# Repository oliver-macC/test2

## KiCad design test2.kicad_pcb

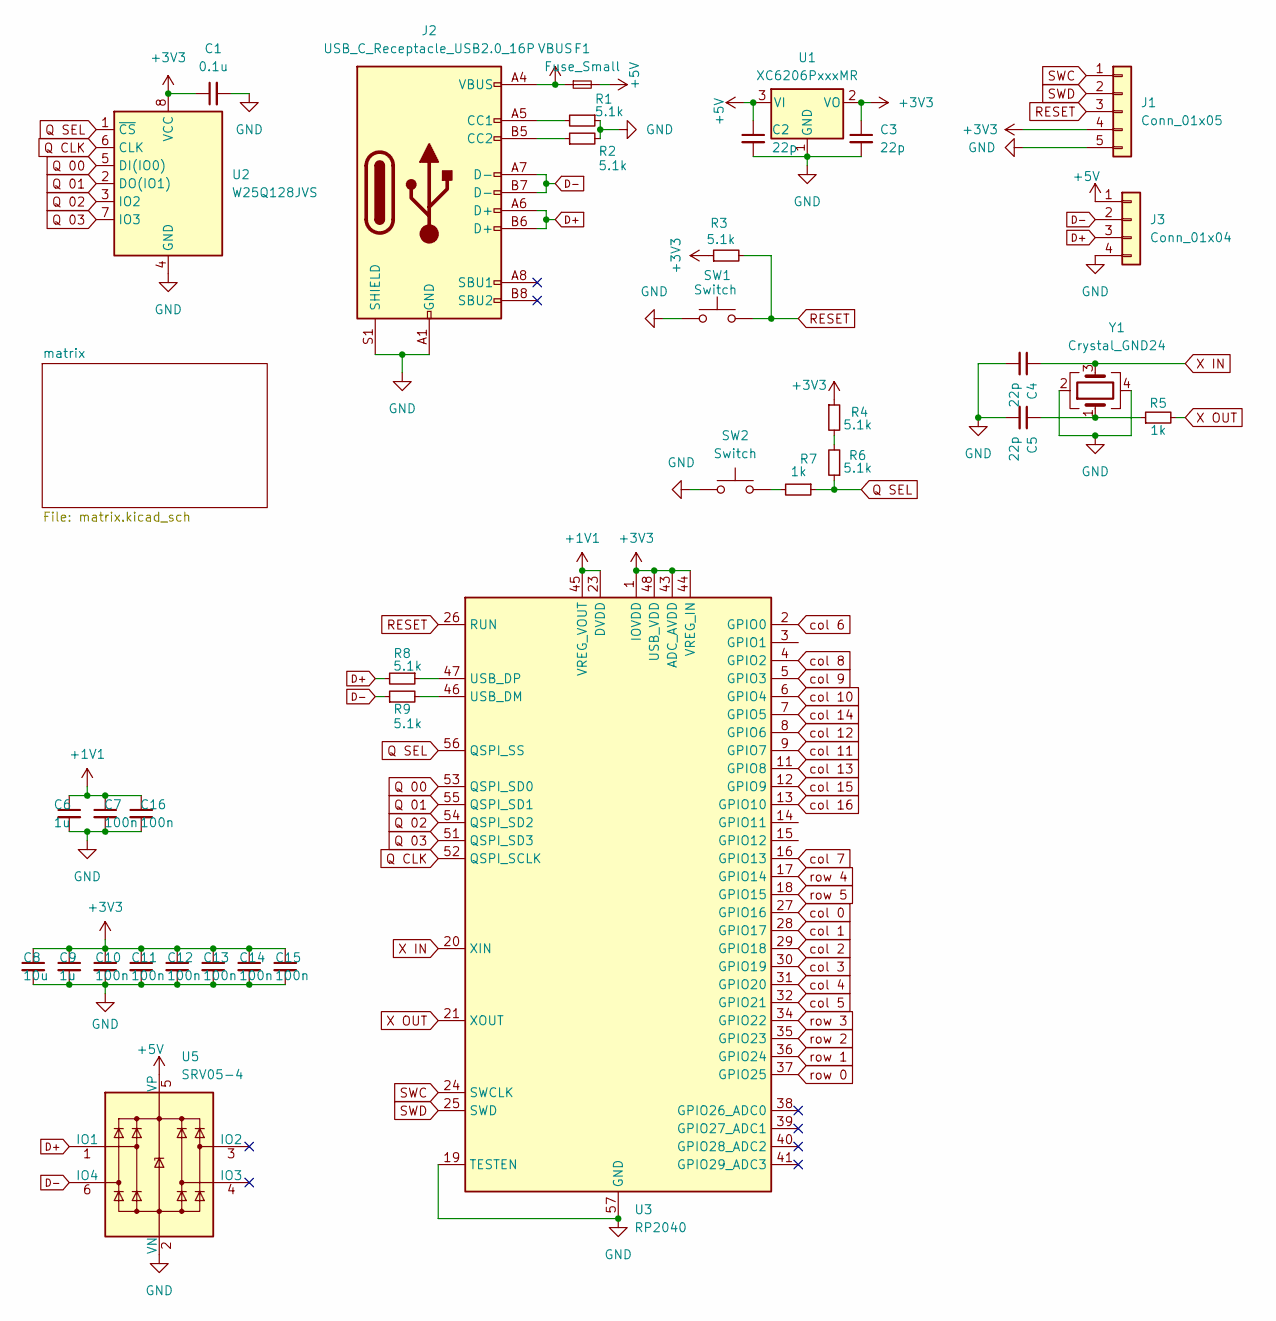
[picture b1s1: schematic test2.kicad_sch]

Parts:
C1: 0.1u; C_0402_1005Metric
C2, C3, C4, C5: 22p; C_0402_1005Metric
C6, C9: 1u; C_0402_1005Metric
C7, C10, C11, C12, C13, C14, C15, C16: 100n; C_0402_1005Metric
C8: 10u; C_0603_1608Metric
F1: Fuse_Small; Fuse_1206_3216Metric
J1: Conn_01x05; PinHeader_1x05_P2.54mm_Vertical
J2: USB_C_Receptacle_USB2.0_16P; USB_C_Receptacle_HRO_TYPE-C-31-M-12
J3: Conn_01x04; JST_SH_SM04B-SRSS-TB_1x04-1MP_P1.00mm_Horizontal
R1, R2, R3, R4, R6, R8, R9: 5.1k; R_0402_1005Metric
R5, R7: 1k; R_0402_1005Metric
SW1, SW2: Switch; SW_Push_1P1T_XKB_TS-1187A
U1: XC6206PxxxMR; SOT-23-3
U2: W25Q128JVS; SOIC-8_5.23x5.23mm_P1.27mm
U3: RP2040; QFN-56-1EP_7x7mm_P0.4mm_EP3.2x3.2mm
U5: SRV05-4; SOT-23-6-routable
Y1: Crystal_GND24; Crystal_SMD_3225-4Pin_3.2x2.5mm

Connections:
+1V1: C6.1, C7.1, C16.1, U3.23 (DVDD), U3.45 (VREG_VOUT), U3.50 (DVDD)
+3V3: C1.1, C3.1, C8.1, C9.1, C10.1, C11.1, C12.1, C13.1, C14.1, C15.1, J1.4, R3.1, R4.1, U1.2 (VO), U2.8 (VCC), U3.1 (IOVDD), U3.10 (IOVDD), U3.22 (IOVDD), U3.33 (IOVDD), U3.42 (IOVDD), U3.43 (ADC_AVDD), U3.44 (VREG_IN), U3.48 (USB_VDD), U3.49 (IOVDD)
+5V: C2.1, F1.2, J3.1, U1.3 (VI), U5.5 (VP)
D+: J2.A6 (D+), J2.B6 (D+), J3.3, R8.2, U5.1 (IO1)
D-: J2.A7 (D-), J2.B7 (D-), J3.2, R9.1, U5.6 (IO4)
GND: C1.2, C2.2, C3.2, C4.2, C5.2, C6.2, C7.2, C8.2, C9.2, C10.2, C11.2, C12.2, C13.2, C14.2, C15.2, C16.2, J1.5, J2.A1 (GND), J2.A12 (GND), J2.B1 (GND), J2.B12 (GND), J2.S1 (SHIELD), J3.4, R1.1, R2.2, SW1.1, SW2.1, U1.1 (GND), U2.4 (GND), U3.19 (TESTEN), U3.57 (GND), U5.2 (VN), Y1.2, Y1.4
unnamed: C5.1, R5.1, Y1.1
unnamed: J2.A5 (CC1), R1.2
unnamed: J2.B5 (CC2), R2.1
unnamed: R4.2, R6.2
unnamed: R7.2, SW2.2
unnamed: R9.2, U3.46 (USB_DM)
unnamed: R8.1, U3.47 (USB_DP)
Q 00: U2.5 (DI(IO0)), U3.53 (QSPI_SD0)
Q 01: U2.2 (DO(IO1)), U3.55 (QSPI_SD1)
Q 02: U2.3 (IO2), U3.54 (QSPI_SD2)
Q 03: U2.7 (IO3), U3.51 (QSPI_SD3)
Q CLK: U2.6 (CLK), U3.52 (QSPI_SCLK)
Q SEL: R6.1, R7.1, U2.1 (~CS), U3.56 (QSPI_SS)
RESET: J1.3, R3.2, SW1.2, U3.26 (RUN)
SWC: J1.1, U3.24 (SWCLK)
SWD: J1.2, U3.25 (SWD)
VBUS: F1.1, J2.A4 (VBUS), J2.A9 (VBUS), J2.B4 (VBUS), J2.B9 (VBUS)
X IN: C4.1, U3.20 (XIN), Y1.3
X OUT: R5.2, U3.21 (XOUT)
col 0: U3.27 (GPIO16); also elsewhere on the board
col 1: U3.28 (GPIO17); also elsewhere on the board
col 2: U3.29 (GPIO18); also elsewhere on the board
col 3: U3.30 (GPIO19); also elsewhere on the board
col 4: U3.31 (GPIO20); also elsewhere on the board
col 5: U3.32 (GPIO21); also elsewhere on the board
col 6: U3.2 (GPIO0); also elsewhere on the board
col 7: U3.16 (GPIO13); also elsewhere on the board
col 8: U3.4 (GPIO2); also elsewhere on the board
col 9: U3.5 (GPIO3); also elsewhere on the board
col 10: U3.6 (GPIO4); also elsewhere on the board
col 11: U3.9 (GPIO7); also elsewhere on the board
col 12: U3.8 (GPIO6); also elsewhere on the board
col 13: U3.11 (GPIO8); also elsewhere on the board
col 14: U3.7 (GPIO5); also elsewhere on the board
col 15: U3.12 (GPIO9); also elsewhere on the board
col 16: U3.13 (GPIO10); also elsewhere on the board
row 0: U3.37 (GPIO25); also elsewhere on the board
row 1: U3.36 (GPIO24); also elsewhere on the board
row 2: U3.35 (GPIO23); also elsewhere on the board
row 3: U3.34 (GPIO22); also elsewhere on the board
row 4: U3.17 (GPIO14); also elsewhere on the board
row 5: U3.18 (GPIO15); also elsewhere on the board

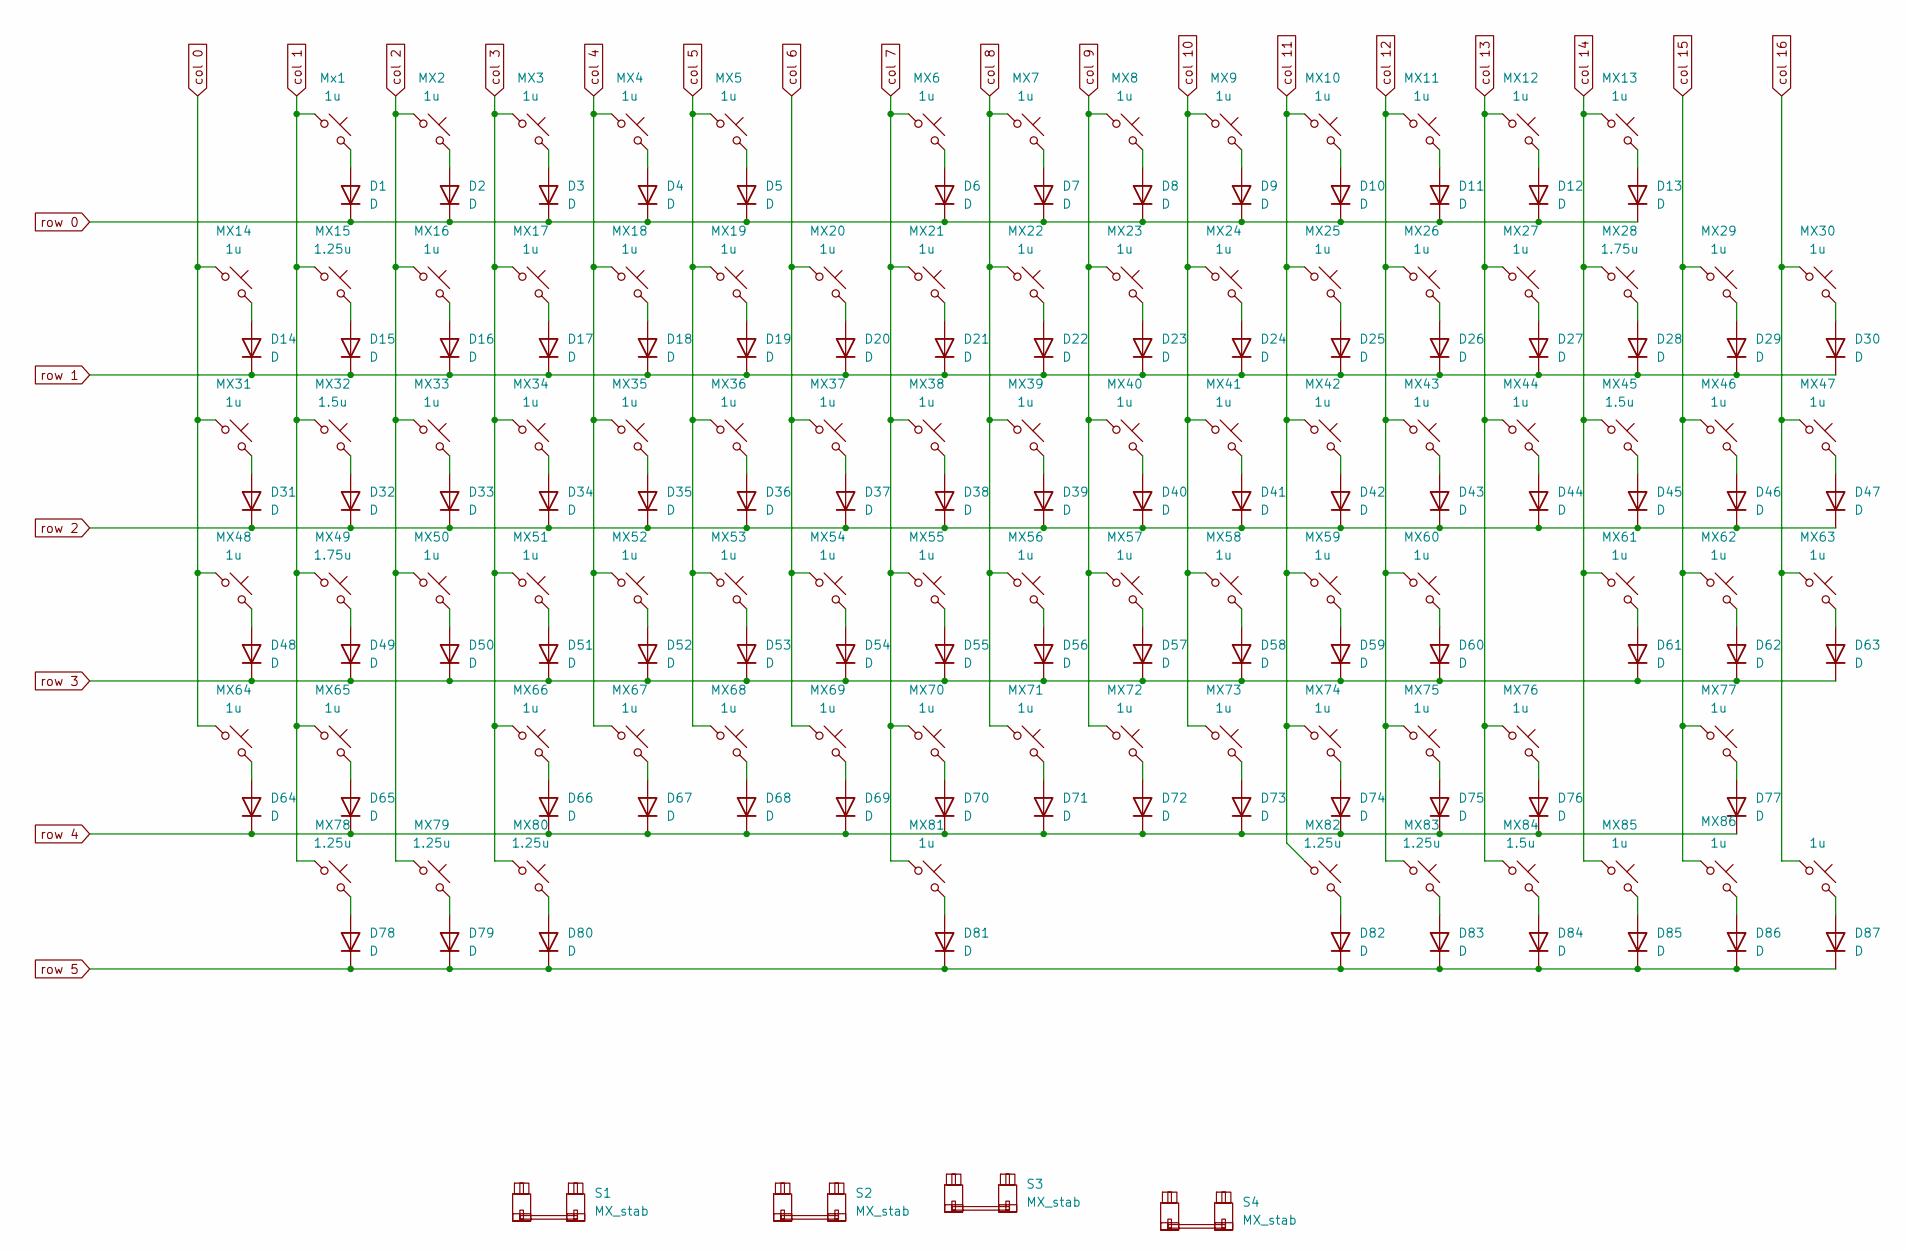
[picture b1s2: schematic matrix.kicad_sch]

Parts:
D1, D2, D3, D4, D5, D6, D7, D8, D9, D10, D11, D12, D13, D14, D15, D16, D17, D18, D19, D20, D21, D22, D23, D24, D25, D26, D27, D28, D29, D30, D31, D32, D33, D34, D35, D36, D37, D38, D39, D40, D41, D42, D43, D44, D45, D46, D47, D48, D49, D50, D51, D52, D53, D54, D55, D56, D57, D58, D59, D60, D61, D62, D63, D64, D65, D66, D67, D68, D69, D70, D71, D72, D73, D74, D75, D76, D77, D78, D79, D80, D81, D82, D83, D84, D85, D86, D87: D; D_SOD-123
MX2, MX3, MX4, MX5, MX6, MX7, MX8, MX9, MX10, MX11, MX12, MX13, MX14, MX16, MX17, MX18, MX19, MX20, MX21, MX22, MX23, MX24, MX25, MX26, MX27, MX29, MX30, MX31, MX33, MX34, MX35, MX36, MX37, MX38, MX39, MX40, MX41, MX42, MX43, MX44, MX46, MX47, MX48, MX50, MX51, MX52, MX53, MX54, MX55, MX56, MX57, MX58, MX59, MX60, MX61, MX62, MX63, MX64, MX65, MX66, MX67, MX68, MX69, MX70, MX71, MX72, MX73, MX74, MX75, MX76, MX77, MX81, MX85, MX86, MX87: 1u; SW_MX_HS_CPG151101S11_1u
MX15, MX78, MX79, MX80, MX82, MX83: 1.25u; SW_MX_HS_CPG151101S11_1.25u
MX28, MX49: 1.75u; SW_MX_HS_CPG151101S11_1.75u
MX32, MX45, MX84: 1.5u; SW_MX_HS_CPG151101S11_1.5u
Mx1: 1u; SW_MX_HS_CPG151101S11_1u
S1: MX_stab; STAB_MX_P_6.25u
S2, S3, S4: MX_stab; STAB_MX_P_2.25u

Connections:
unnamed: D1.2 (A), Mx1.2
unnamed: D2.2 (A), MX2.2
unnamed: D3.2 (A), MX3.2
unnamed: D4.2 (A), MX4.2
unnamed: D5.2 (A), MX5.2
unnamed: D6.2 (A), MX6.2
unnamed: D7.2 (A), MX7.2
unnamed: D8.2 (A), MX8.2
unnamed: D9.2 (A), MX9.2
unnamed: D10.2 (A), MX10.2
unnamed: D11.2 (A), MX11.2
unnamed: D12.2 (A), MX12.2
unnamed: D13.2 (A), MX13.2
unnamed: D14.2 (A), MX14.2
unnamed: D15.2 (A), MX15.2
unnamed: D16.2 (A), MX16.2
unnamed: D17.2 (A), MX17.2
unnamed: D18.2 (A), MX18.2
unnamed: D19.2 (A), MX19.2
unnamed: D20.2 (A), MX20.2
unnamed: D21.2 (A), MX21.2
unnamed: D22.2 (A), MX22.2
unnamed: D23.2 (A), MX23.2
unnamed: D24.2 (A), MX24.2
unnamed: D25.2 (A), MX25.2
unnamed: D26.2 (A), MX26.2
unnamed: D27.2 (A), MX27.2
unnamed: D28.2 (A), MX28.2
unnamed: D29.2 (A), MX29.2
unnamed: D30.2 (A), MX30.2
unnamed: D31.2 (A), MX31.2
unnamed: D32.2 (A), MX32.2
unnamed: D33.2 (A), MX33.2
unnamed: D34.2 (A), MX34.2
unnamed: D35.2 (A), MX35.2
unnamed: D36.2 (A), MX36.2
unnamed: D37.2 (A), MX37.2
unnamed: D38.2 (A), MX38.2
unnamed: D39.2 (A), MX39.2
unnamed: D40.2 (A), MX40.2
unnamed: D41.2 (A), MX41.2
unnamed: D42.2 (A), MX42.2
unnamed: D43.2 (A), MX43.2
unnamed: D44.2 (A), MX44.2
unnamed: D45.2 (A), MX45.2
unnamed: D46.2 (A), MX46.2
unnamed: D47.2 (A), MX47.2
unnamed: D48.2 (A), MX48.2
unnamed: D49.2 (A), MX49.2
unnamed: D50.2 (A), MX50.2
unnamed: D51.2 (A), MX51.2
unnamed: D52.2 (A), MX52.2
unnamed: D53.2 (A), MX53.2
unnamed: D54.2 (A), MX54.2
unnamed: D55.2 (A), MX55.2
unnamed: D56.2 (A), MX56.2
unnamed: D57.2 (A), MX57.2
unnamed: D58.2 (A), MX58.2
unnamed: D59.2 (A), MX59.2
unnamed: D60.2 (A), MX60.2
unnamed: D61.2 (A), MX61.2
unnamed: D62.2 (A), MX62.2
unnamed: D63.2 (A), MX63.2
unnamed: D64.2 (A), MX64.2
unnamed: D65.2 (A), MX65.2
unnamed: D66.2 (A), MX66.2
unnamed: D67.2 (A), MX67.2
unnamed: D68.2 (A), MX68.2
unnamed: D69.2 (A), MX69.2
unnamed: D70.2 (A), MX70.2
unnamed: D71.2 (A), MX71.2
unnamed: D72.2 (A), MX72.2
unnamed: D73.2 (A), MX73.2
unnamed: D74.2 (A), MX74.2
unnamed: D75.2 (A), MX75.2
unnamed: D76.2 (A), MX76.2
unnamed: D77.2 (A), MX77.2
unnamed: D78.2 (A), MX78.2
unnamed: D79.2 (A), MX79.2
unnamed: D80.2 (A), MX80.2
unnamed: D81.2 (A), MX81.2
unnamed: D82.2 (A), MX82.2
unnamed: D83.2 (A), MX83.2
unnamed: D84.2 (A), MX84.2
unnamed: D85.2 (A), MX85.2
unnamed: D86.2 (A), MX86.2
unnamed: D87.2 (A), MX87.2
col 0: MX14.1, MX31.1, MX48.1, MX64.1; also elsewhere on the board
col 1: MX15.1, MX32.1, MX49.1, MX65.1, MX78.1, Mx1.1; also elsewhere on the board
col 2: MX2.1, MX16.1, MX33.1, MX50.1, MX79.1; also elsewhere on the board
col 3: MX3.1, MX17.1, MX34.1, MX51.1, MX66.1, MX80.1; also elsewhere on the board
col 4: MX4.1, MX18.1, MX35.1, MX52.1, MX67.1; also elsewhere on the board
col 5: MX5.1, MX19.1, MX36.1, MX53.1, MX68.1; also elsewhere on the board
col 6: MX20.1, MX37.1, MX54.1, MX69.1; also elsewhere on the board
col 7: MX6.1, MX21.1, MX38.1, MX55.1, MX70.1, MX81.1; also elsewhere on the board
col 8: MX7.1, MX22.1, MX39.1, MX56.1, MX71.1; also elsewhere on the board
col 9: MX8.1, MX23.1, MX40.1, MX57.1, MX72.1; also elsewhere on the board
col 10: MX9.1, MX24.1, MX41.1, MX58.1, MX73.1; also elsewhere on the board
col 11: MX10.1, MX25.1, MX42.1, MX59.1, MX74.1, MX82.1; also elsewhere on the board
col 12: MX11.1, MX26.1, MX43.1, MX60.1, MX75.1, MX83.1; also elsewhere on the board
col 13: MX12.1, MX27.1, MX44.1, MX76.1, MX84.1; also elsewhere on the board
col 14: MX13.1, MX28.1, MX45.1, MX61.1, MX85.1; also elsewhere on the board
col 15: MX29.1, MX46.1, MX62.1, MX77.1, MX86.1; also elsewhere on the board
col 16: MX30.1, MX47.1, MX63.1, MX87.1; also elsewhere on the board
row 0: D1.1 (K), D2.1 (K), D3.1 (K), D4.1 (K), D5.1 (K), D6.1 (K), D7.1 (K), D8.1 (K), D9.1 (K), D10.1 (K), D11.1 (K), D12.1 (K), D13.1 (K); also elsewhere on the board
row 1: D14.1 (K), D15.1 (K), D16.1 (K), D17.1 (K), D18.1 (K), D19.1 (K), D20.1 (K), D21.1 (K), D22.1 (K), D23.1 (K), D24.1 (K), D25.1 (K), D26.1 (K), D27.1 (K), D28.1 (K), D29.1 (K), D30.1 (K); also elsewhere on the board
row 2: D31.1 (K), D32.1 (K), D33.1 (K), D34.1 (K), D35.1 (K), D36.1 (K), D37.1 (K), D38.1 (K), D39.1 (K), D40.1 (K), D41.1 (K), D42.1 (K), D43.1 (K), D44.1 (K), D45.1 (K), D46.1 (K), D47.1 (K); also elsewhere on the board
row 3: D48.1 (K), D49.1 (K), D50.1 (K), D51.1 (K), D52.1 (K), D53.1 (K), D54.1 (K), D55.1 (K), D56.1 (K), D57.1 (K), D58.1 (K), D59.1 (K), D60.1 (K), D61.1 (K), D62.1 (K), D63.1 (K); also elsewhere on the board
row 4: D64.1 (K), D65.1 (K), D66.1 (K), D67.1 (K), D68.1 (K), D69.1 (K), D70.1 (K), D71.1 (K), D72.1 (K), D73.1 (K), D74.1 (K), D75.1 (K), D76.1 (K), D77.1 (K); also elsewhere on the board
row 5: D78.1 (K), D79.1 (K), D80.1 (K), D81.1 (K), D82.1 (K), D83.1 (K), D84.1 (K), D85.1 (K), D86.1 (K), D87.1 (K); also elsewhere on the board

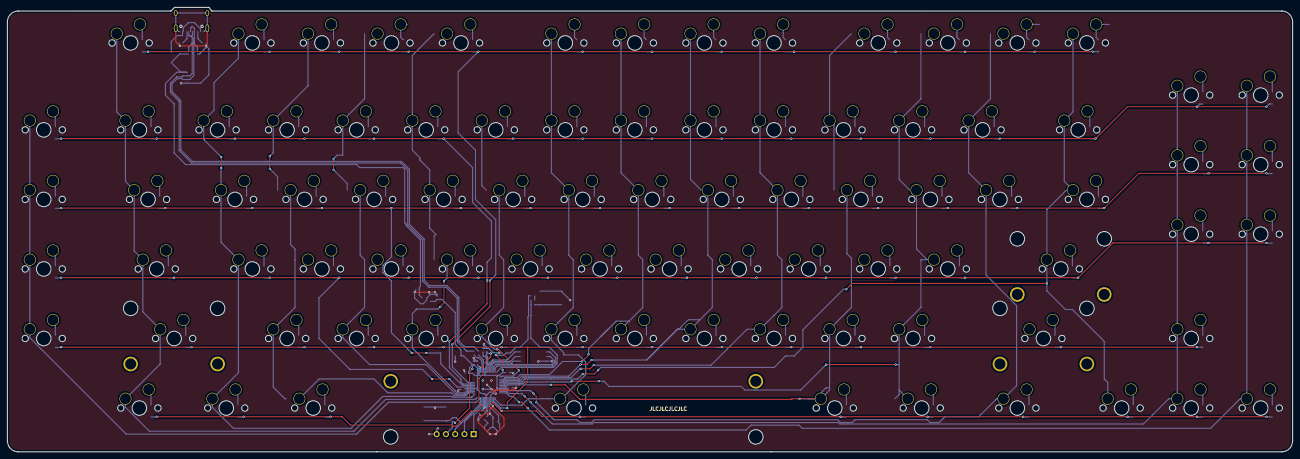
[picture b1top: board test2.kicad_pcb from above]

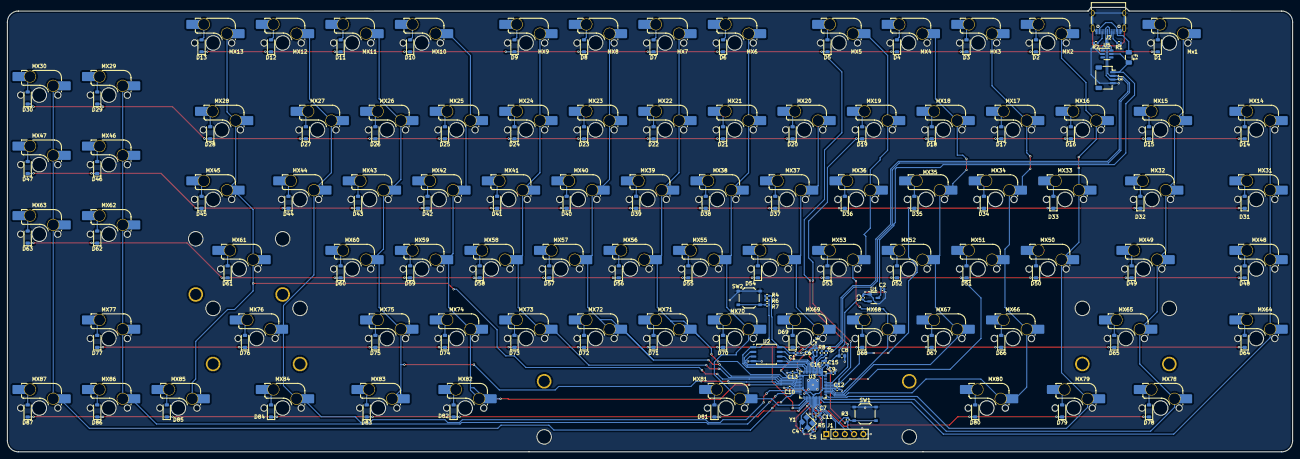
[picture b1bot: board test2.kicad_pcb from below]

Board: 2 copper layers, 352.1 x 121.7 mm, 214 parts (210 on the bottom side), 135 nets.

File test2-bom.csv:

Id,Designator,Footprint,Quantity,Designation,Supplier and ref
1,"MX84,MX45,MX32",SW_MX_HS_CPG151101S11_1.5u,3,1.5u MX CPG151101S11,
2,"D19,D51,D27,D42,D48,D20,D45,D82,D17,D70,D5,D23,D38,D54,D41,D86,D77,D50,D72,D78,D13,D30,D8,D73,D6,D56,D55,D31,D80,D24,D69,D57,D46,D49,D7,D11,D59,D67,D61,D83,D43,D40,D64,D2,D26,D58,D74,D76,D18,D68,D28,D32,D15,D25,D14,D79,D3,D1,D71,D65,D47,D63,D9,D44,D60,D84,D22,D10,D35,D36,D21,D81,D33,D16,D12,D37,D66,D87,D62,D39,D4,D53,D52,D75,D85,D29,D34",D_SOD-123,87,SOD-123,
3,"MX28,MX49",SW_MX_HS_CPG151101S11_1.75u,2,1.75u MX CPG151101S11,
4,"MX81,MX12,MX21,MX36,MX20,MX52,MX70,MX11,MX74,MX71,MX43,MX86,MX23,MX3,MX17,MX10,MX7,MX57,MX47,MX40,MX44,MX42,MX54,MX72,MX73,MX27,MX61,MX62,MX56,MX55,MX87,MX8,MX41,MX39,MX14,MX59,MX26,MX63,MX75,MX38,MX2,MX85,MX51,MX77,MX50,MX34,MX60,MX5,MX65,MX67,MX46,MX66,MX30,MX29,MX53,MX33,MX76,MX64,MX19,MX58,MX9,MX69,MX31,MX4,MX24,MX48,MX22,MX37,MX6,Mx1,MX35,MX18,MX25,MX68,MX13,MX16",SW_MX_HS_CPG151101S11_1u,76,1u MX CPG151101S11,
5,U1,SOT-23-3,1,XC6206PxxxMR,
6,"R2,R1,R4,R6,R8,R9,R3",R_0402_1005Metric,7,5.1k,
7,"MX79,MX83,MX78,MX15,MX80,MX82",SW_MX_HS_CPG151101S11_1.25u,6,1.25u MX CPG151101S11,
8,"R5,R7",R_0402_1005Metric,2,1k 0402,
9,"C9,C6",C_0402_1005Metric,2,1u 0402,
10,"C12,C16,C11,C15,C7,C13,C14,C10",C_0402_1005Metric,8,100n 0402,
11,Y1,Crystal_SMD_3225-4Pin_3.2x2.5mm,1,Crystal_GND24,
12,"C5,C4,C2,C3",C_0402_1005Metric,4,22p 0402,
13,J2,USB_C_Receptacle_HRO_TYPE-C-31-M-12,1,HRO_TYPE-C-31-M-12,
14,U2,SOIC-8_5.23x5.23mm_P1.27mm,1,W25Q128JVS,
15,"SW2,SW1",SW_Push_1P1T_XKB_TS-1187A,2,Switch,
16,U5,SOT-23-6-routable,1,SRV05-4,
17,J3,JST_SH_SM04B-SRSS-TB_1x04-1MP_P1.00mm_Horizontal,1,Conn_01x04 SM04B-SRSS-TB_1x04-1MP_P1.00mm_Horizontal,
18,J1,PinHeader_1x05_P2.54mm_Vertical,1,Conn_01x05 PinHeader_1x05_P2.54mm_Vertical,
19,C8,C_0603_1608Metric,1,10u 0603,
20,C1,C_0402_1005Metric,1,1u 0402,
21,U3,QFN-56-1EP_7x7mm_P0.4mm_EP3.2x3.2mm,1,RP2040,
22,F1,Fuse_1206_3216Metric,1,1206,

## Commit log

2024-08-27 project resumed
2024-09-20 Finalization of 89 key
    Changed 104 keys to 89, removed LEDs, created files needed for production.
